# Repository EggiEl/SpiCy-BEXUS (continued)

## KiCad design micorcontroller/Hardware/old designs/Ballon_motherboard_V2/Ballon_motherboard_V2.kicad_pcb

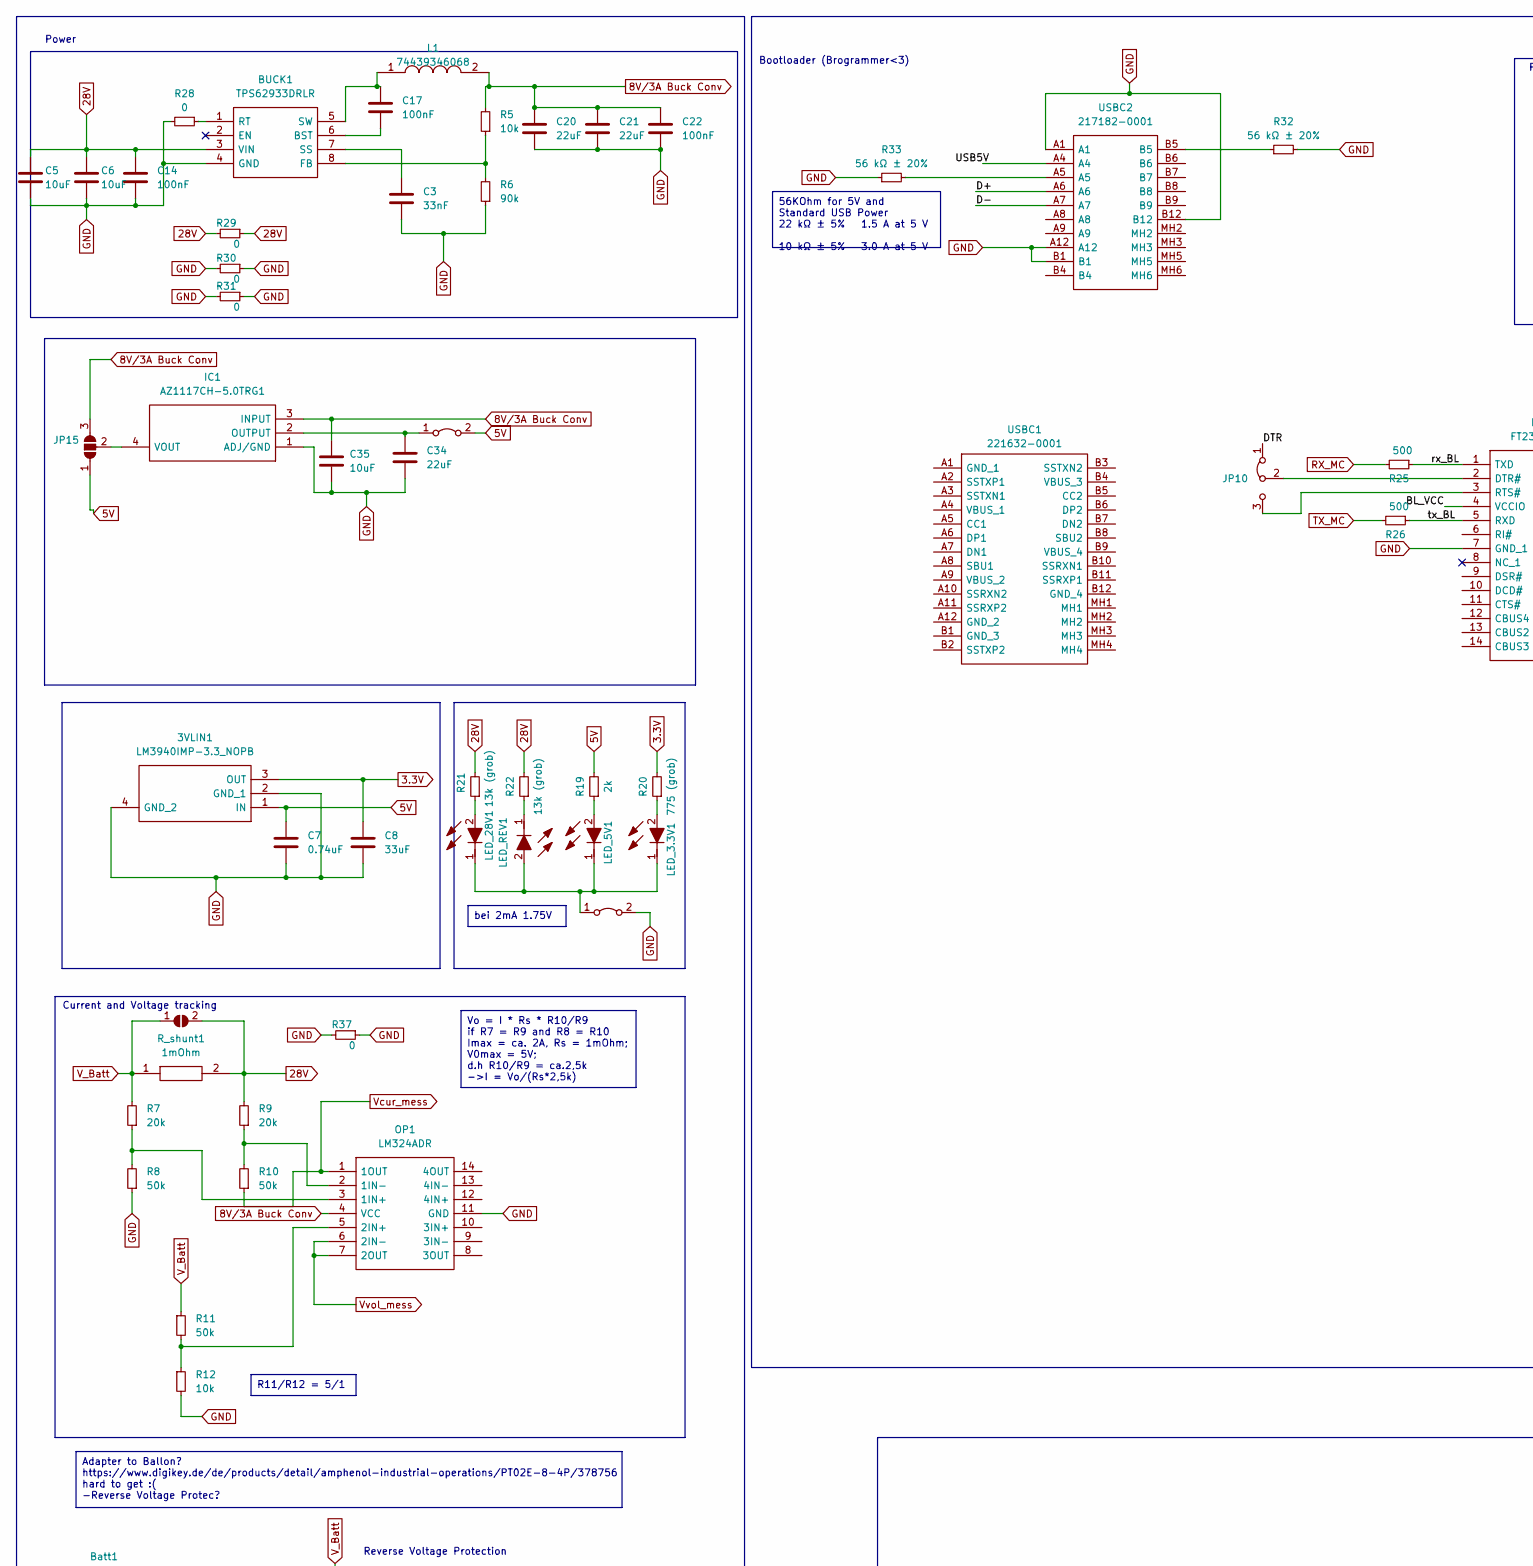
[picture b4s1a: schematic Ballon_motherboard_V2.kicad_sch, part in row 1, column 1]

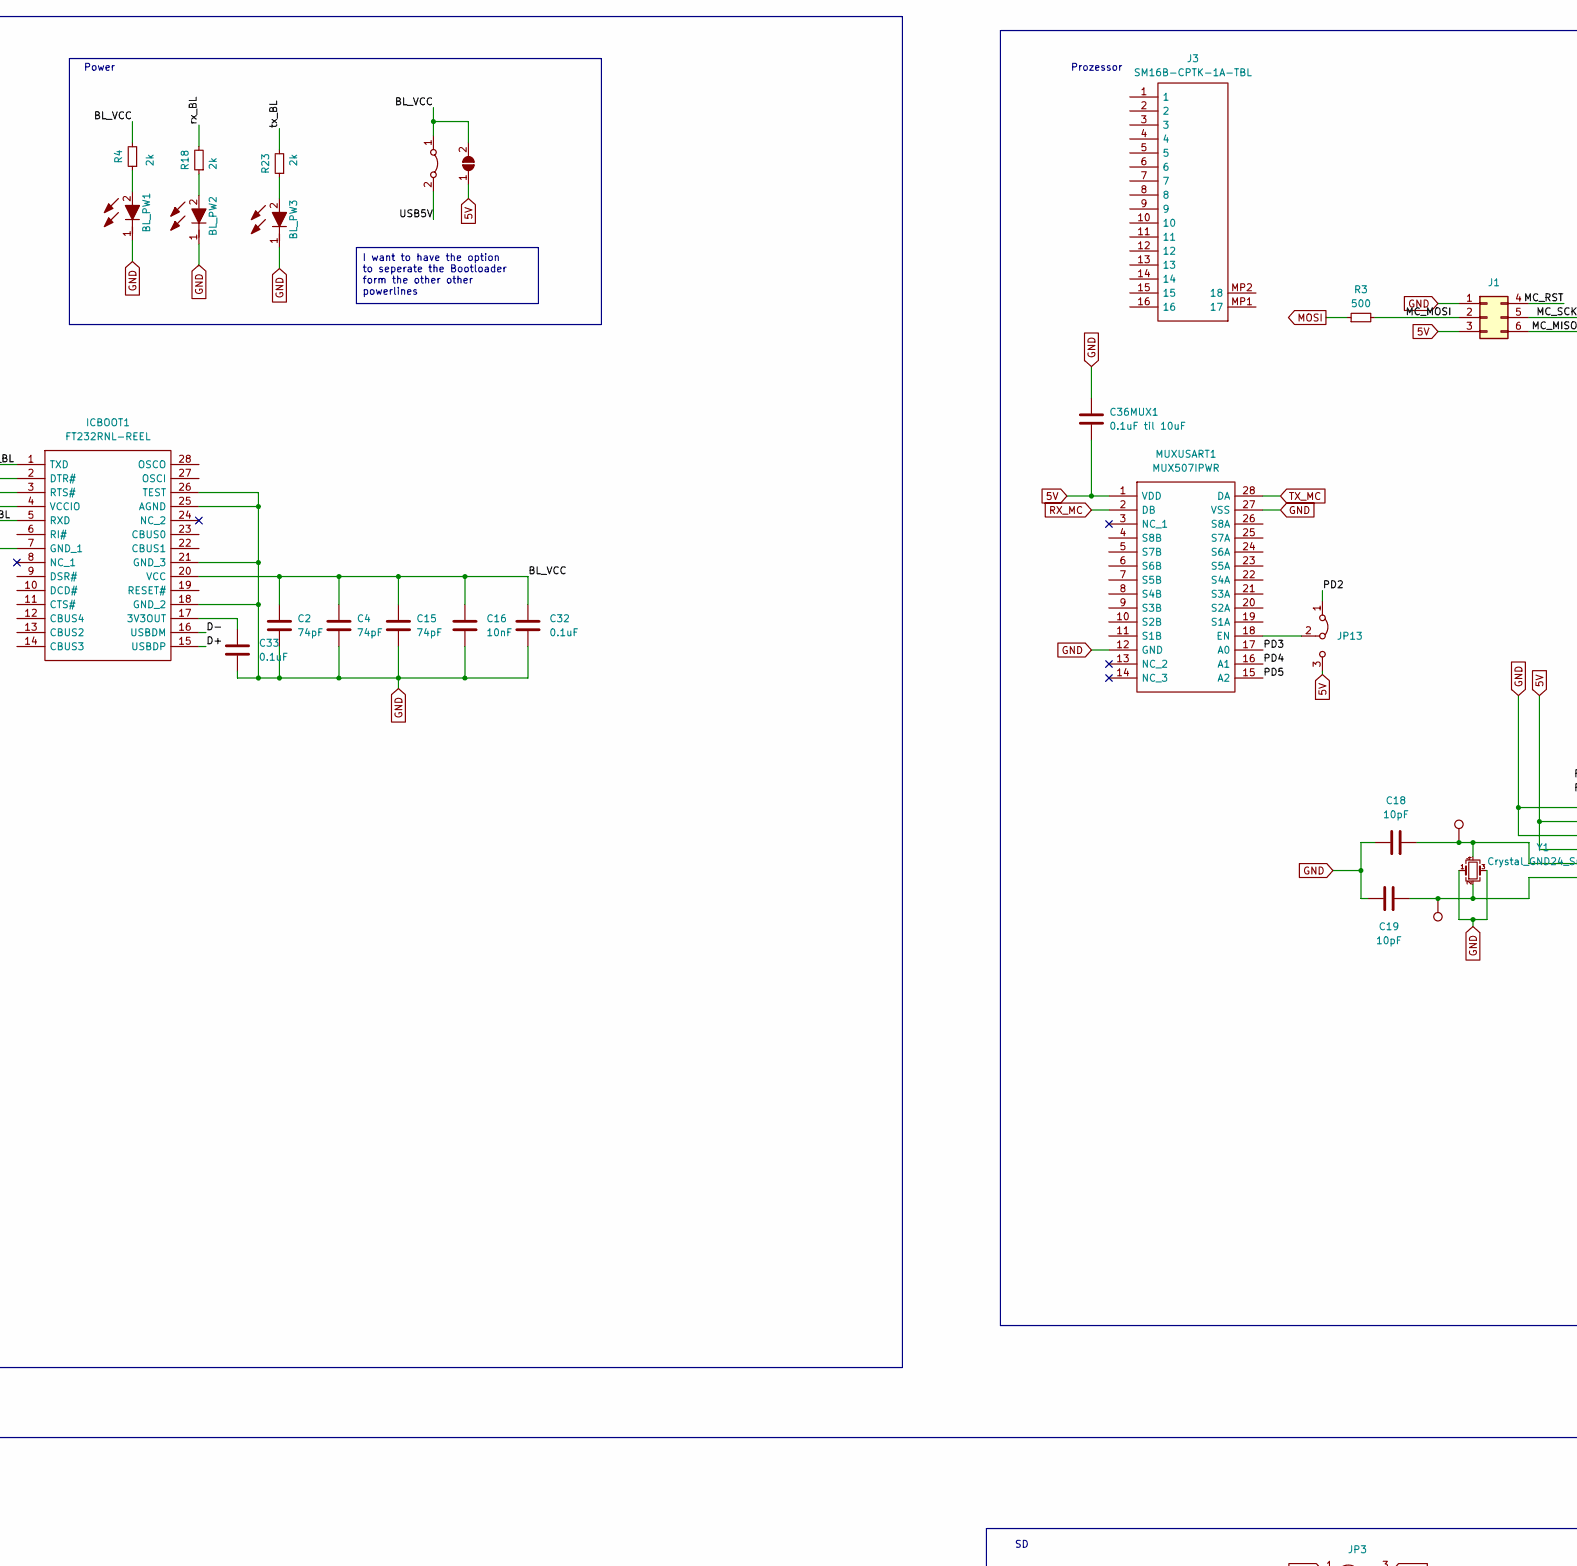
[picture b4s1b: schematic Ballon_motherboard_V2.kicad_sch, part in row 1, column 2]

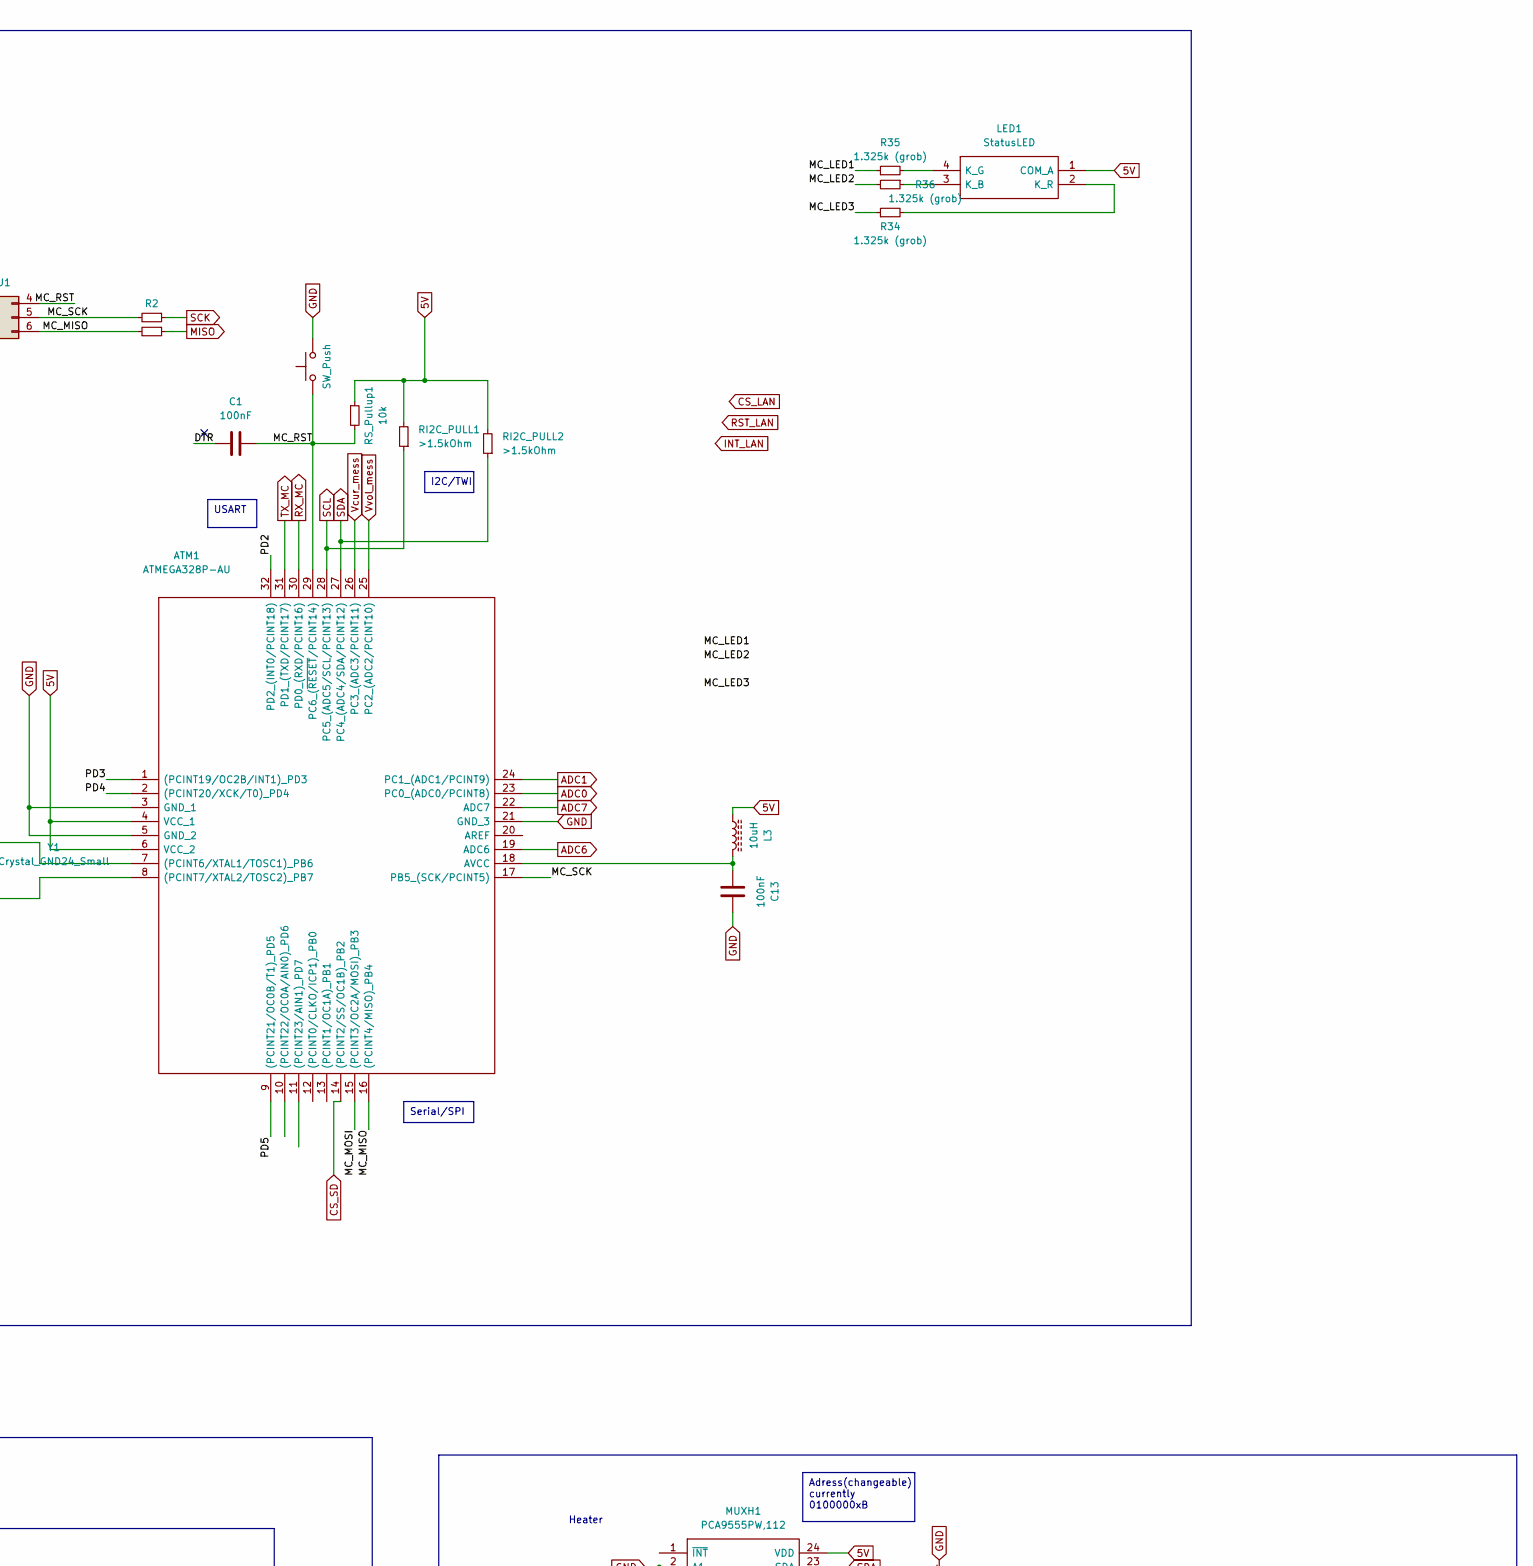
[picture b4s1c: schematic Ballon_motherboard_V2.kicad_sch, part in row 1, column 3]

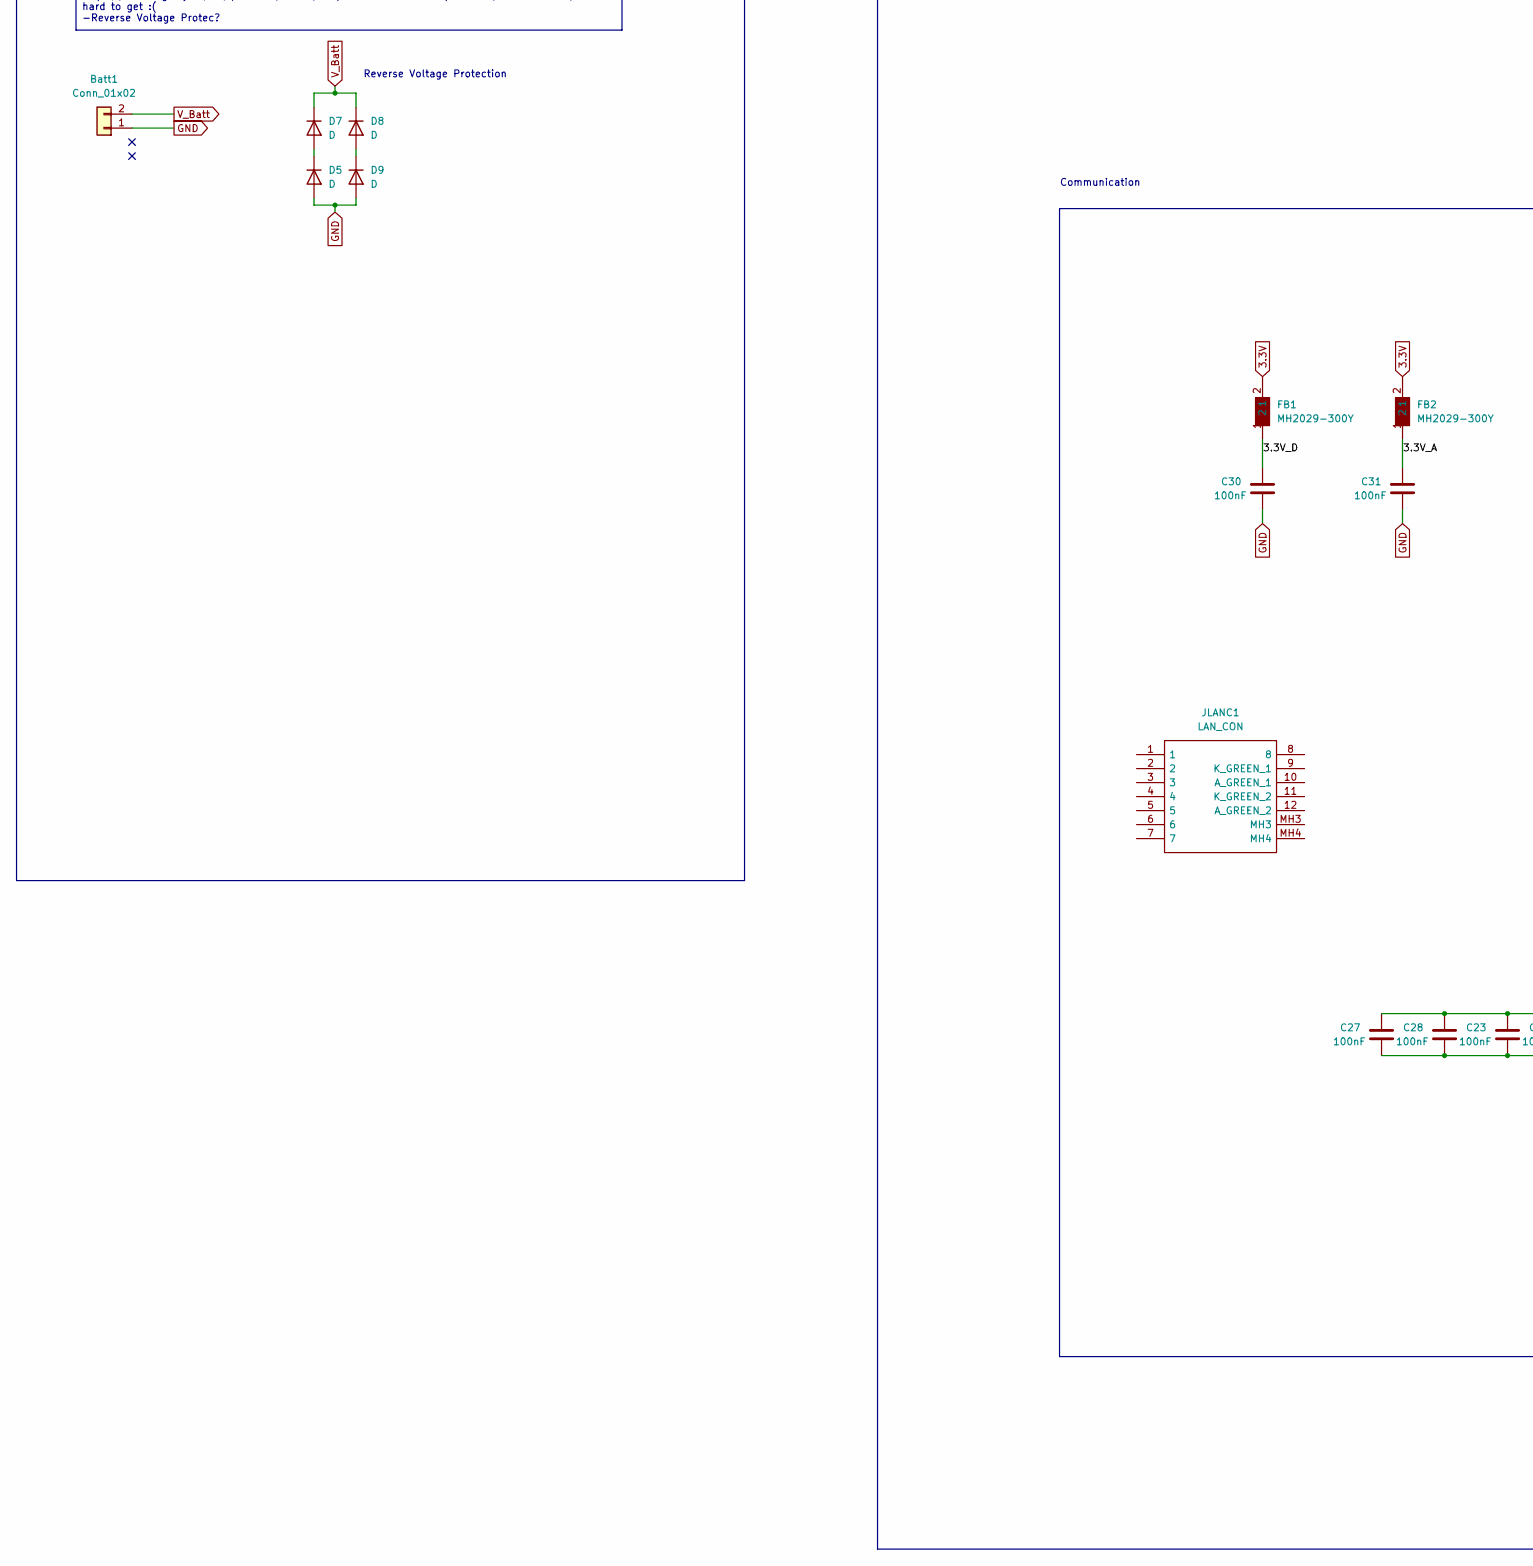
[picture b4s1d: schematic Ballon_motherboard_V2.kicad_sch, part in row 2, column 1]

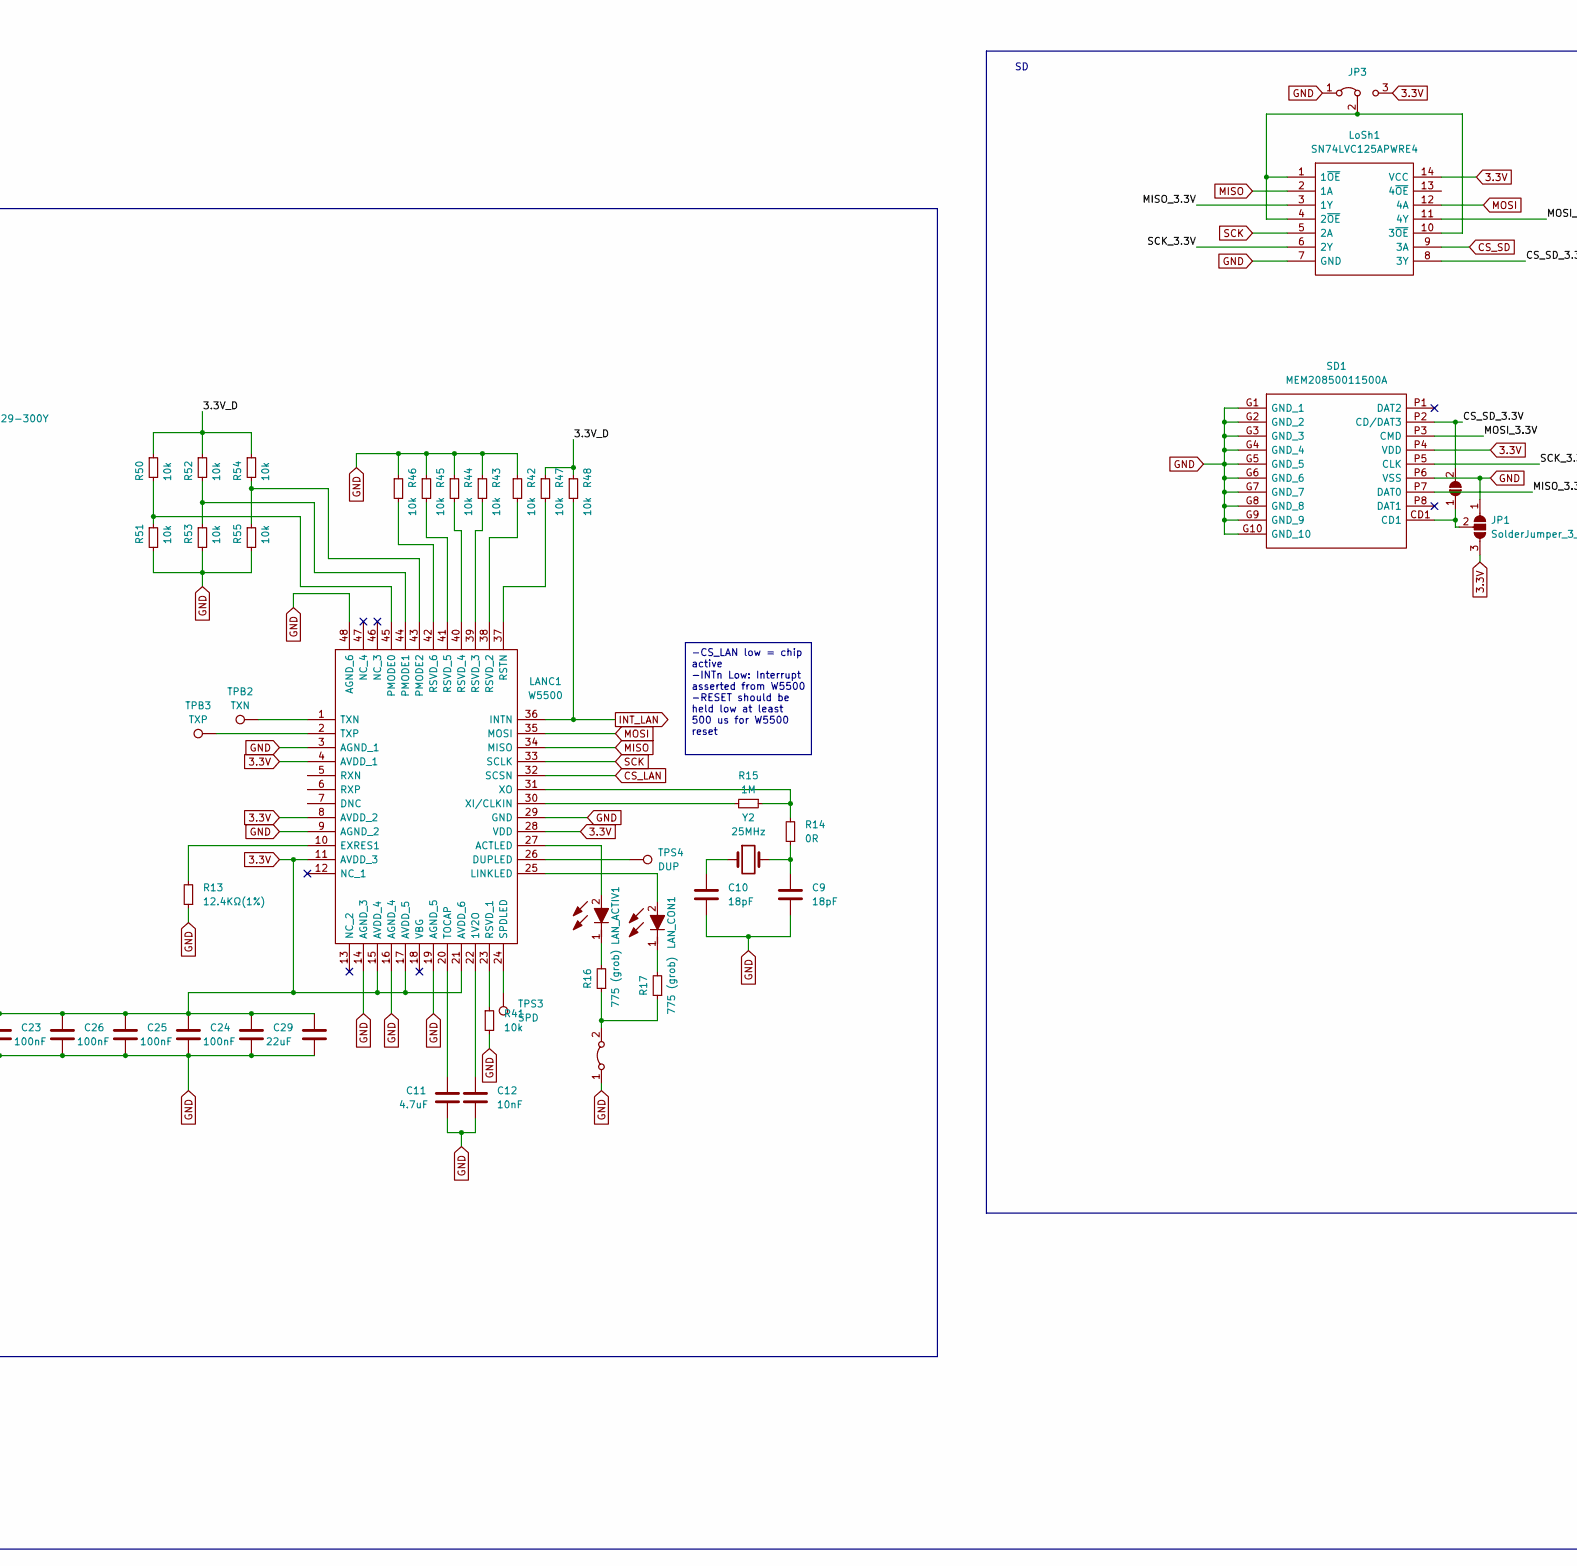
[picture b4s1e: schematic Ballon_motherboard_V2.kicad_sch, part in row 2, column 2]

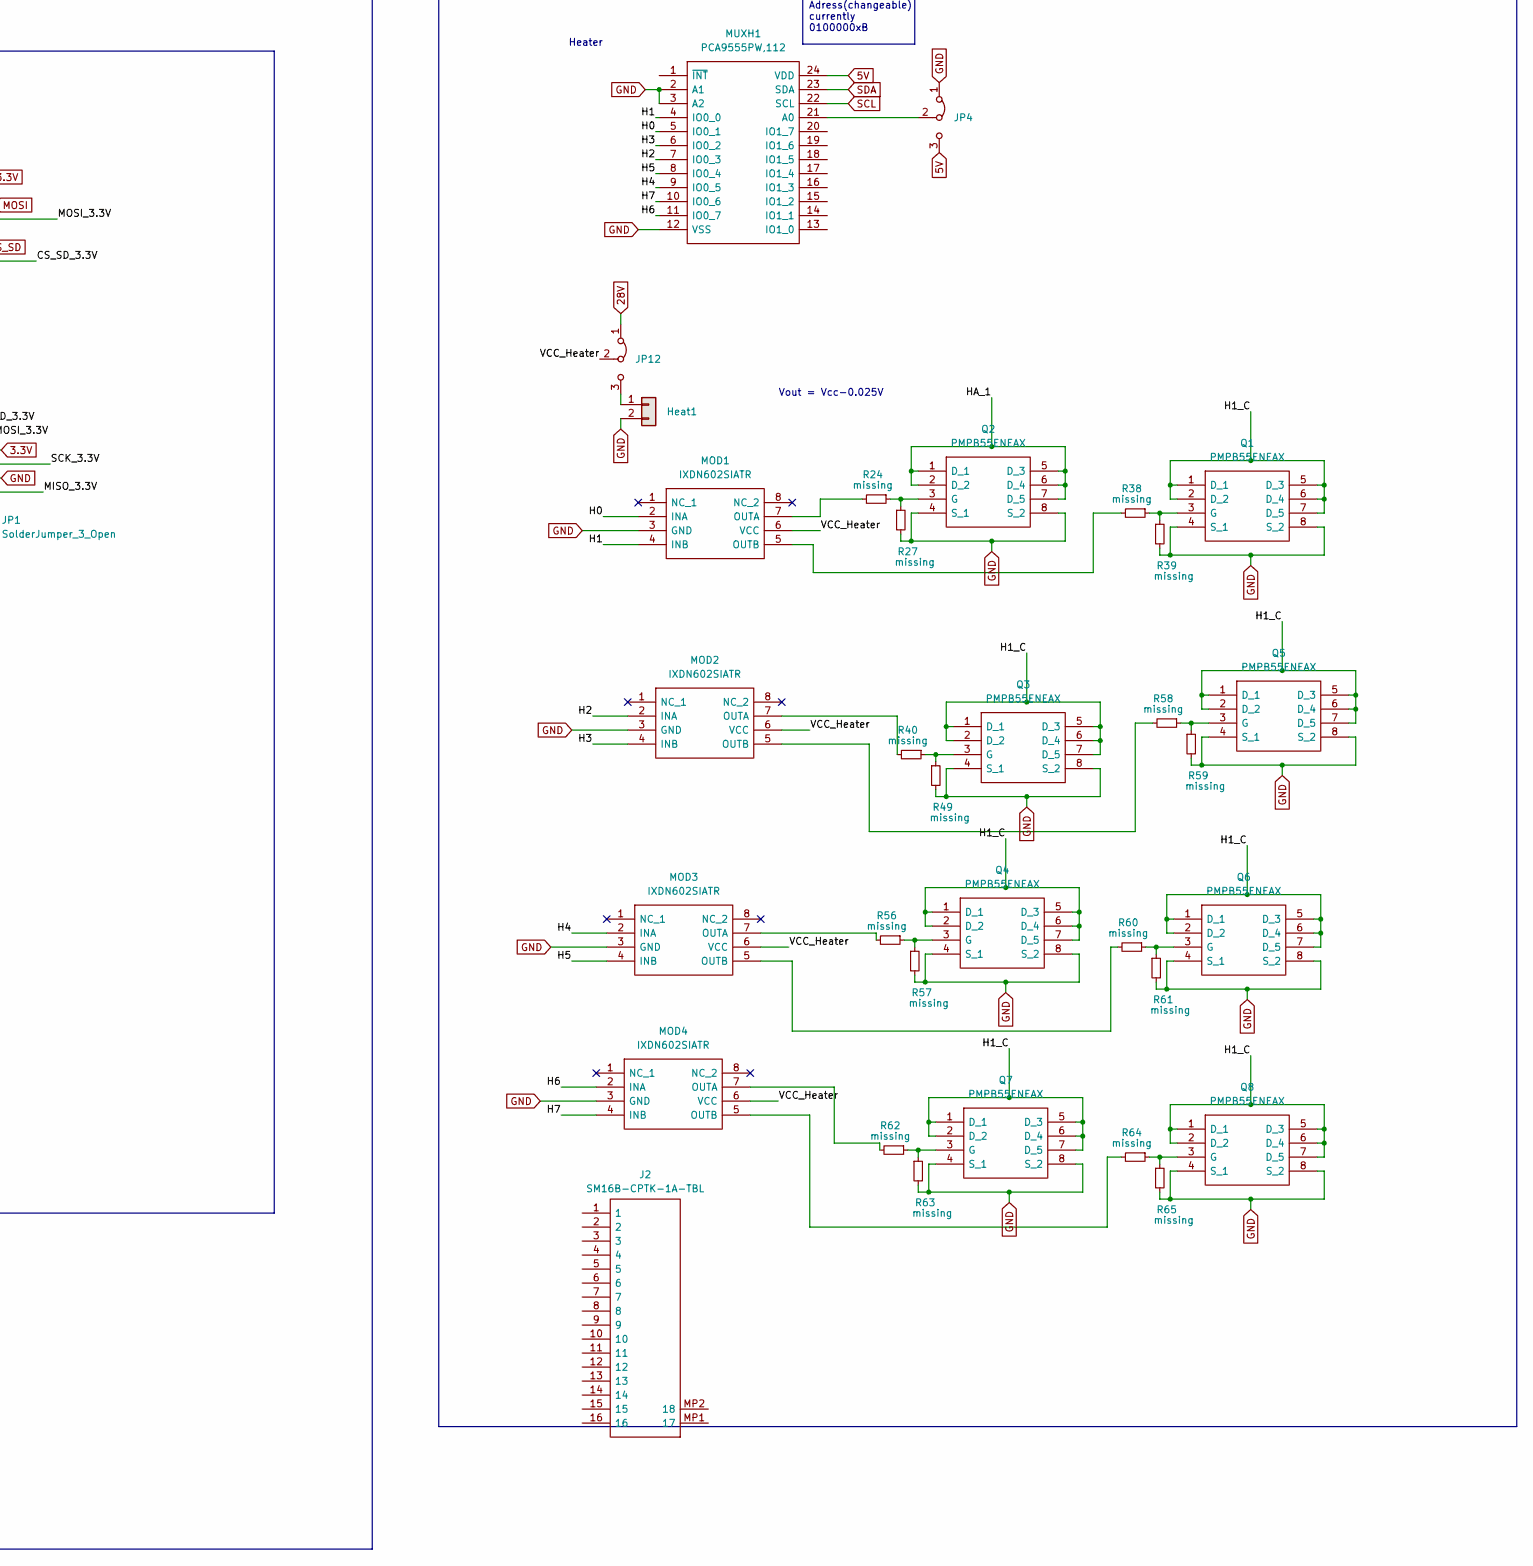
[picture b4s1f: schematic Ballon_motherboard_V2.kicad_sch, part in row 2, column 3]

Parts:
3VLIN1: LM3940IMP-3.3_NOPB; SOT230P700X180-4N; Mouser Part Number 926-LM3940IMP3.3NOPB
ATM1: ATMEGA328P-AU; QFP80P900X900X120-32N; Mouser Part Number 556-ATMEGA328P-AU
BL_PW1, BL_PW2, BL_PW3: APTD2012LSURCK; LEDM2012X120N; Mouser Part Number 604-APTD2012LSURCK
BUCK1: TPS62933DRLR; SOTFL50P160X60-8N; Mouser Part Number 595-TPS62933DRLR
Batt1: Conn_01x02; PinHeader_1x02_P2.54mm_Vertical
C1, C13, C14, C17, C22, C23, C24, C25, C26, C27, C28, C30, C31: 100nF; C_0603_1608Metric
C2, C4, C15: 74pF; C_0603_1608Metric
C3: 33nF; C_0603_1608Metric
C5, C6, C35: 10uF; C_0603_1608Metric
C7: 0.74uF; C_0603_1608Metric
C8: 33uF; C_0603_1608Metric
C9, C10: 18pF; C_0603_1608Metric
C11: 4.7uF; C_0603_1608Metric
C12, C16: 10nF; C_0603_1608Metric
C18, C19: 10pF; C_0603_1608Metric
C20, C21, C29, C34: 22uF; C_0603_1608Metric
C32, C33: 0.1uF; C_0603_1608Metric
C36MUX1: 0.1uF til 10uF; C_0603_1608Metric
D5, D7, D8, D9: D
FB1, FB2: MH2029-300Y; BEADC2016X130N; Mouser Part Number 652-MH2029-300Y
Heat1: Conn_01x02; PinHeader_1x02_P2.54mm_Vertical
IC1: AZ1117CH-5.0TRG1; SOT230P700X180-4N; Mouser Part Number 621-AZ1117CH-5.0TRG1
ICBOOT1: FT232RNL-REEL; SOP65P780X200-28N; Mouser Part Number 895-FT232RNL-REEL
J1: Conn_02x03_Top_Bottom; PinHeader_2x03_P2.54mm_Vertical
J2, J3: SM16B-CPTK-1A-TBL; SM16BCPTK1ATBL; Mouser Part Number 306-SM16B-CPTK-1ATBL
JLANC1: LAN_CON; MJ323088GG2; Mouser Part Number 640-MJ323088GG2
JP1, JP15: SolderJumper_3_Open; SolderJumper-3_P1.3mm_Open_RoundedPad1.0x1.5mm_NumberLabels
JP2, JP8, JP11: SolderJumper_2_Open; SolderJumper-2_P1.3mm_Open_Pad1.0x1.5mm
JP3, JP4, JP10, JP12, JP13: Jumper_3_Bridged12; SolderJumper-3_P1.3mm_Bridged12_RoundedPad1.0x1.5mm_NumberL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
JP5, JP6, JP7, JP9: Jumper_2_Bridged; SolderJumper-2_P1.3mm_Bridged2Bar_RoundedPad1.0x1.5mm
L1: 74439346068; Mouser Part Number 710-74439346068
L3: 10uH
LANC1: W5500; QFP50P900X900X160-48N; Mouser Part Number 950-W5500
LAN_ACTIV1: APTD2012LSURCK; LEDM2012X120N; Mouser Part Number 604-APTD2012LSURCK
LAN_CON1: APTD2012LSURCK; LEDM2012X120N; Mouser Part Number 604-APTD2012LSURCK
LED1: StatusLED; LTRBR37G4R4S01250; Mouser Part Number 720-LTRBR37GA6714
LED_3.3V1, LED_5V1, LED_28V1: APTD2012LSURCK; LEDM2012X120N; Mouser Part Number 604-APTD2012LSURCK
LED_REV1: APTD2012LSURCK; LEDM2012X120N; Mouser Part Number 604-APTD2012LSURCK
LoSh1: SN74LVC125APWRE4; Mouser Part Number 595-SN74LVC125APWRE4
MOD1, MOD2, MOD3, MOD4: IXDN602SIATR; SOIC127P600X175-8N; Mouser Part Number 849-IXDN602SIATR
MUXH1: PCA9555PW,112; SOP65P640X110-24N; Mouser Part Number 771-PCA9555PW
MUXUSART1: MUX507IPWR; SOP65P640X120-28N; Mouser Part Number 595-MUX507IPWR
OP1: LM324ADR; SOIC127P600X175-14N; Mouser Part Number 595-LM324ADR
Q1, Q2, Q3, Q4, Q5, Q6, Q7, Q8: PMPB55ENEAX; Mouser Part Number 771-PMPB55ENEAX
R1, R2, R3: 500; R_0805_2012Metric_Pad1.20x1.40mm_HandSolder
R4, R18, R19, R23: 2k; R_0805_2012Metric_Pad1.20x1.40mm_HandSolder
R5, R12, R41, R42, R43, R44, R45, R46, R47, R48, R50, R51, R52, R53, R54, R55: 10k; R_0805_2012Metric_Pad1.20x1.40mm_HandSolder
R6: 90k; R_0805_2012Metric_Pad1.20x1.40mm_HandSolder
R7, R9: 20k; R_0805_2012Metric_Pad1.20x1.40mm_HandSolder
R8, R10, R11: 50k; R_0805_2012Metric_Pad1.20x1.40mm_HandSolder
R13: 12.4KΩ(1%); R_0805_2012Metric_Pad1.20x1.40mm_HandSolder
R14: 0R; R_0805_2012Metric
R15: 1M; R_0805_2012Metric_Pad1.20x1.40mm_HandSolder
R16, R17, R20: 775 (grob); R_0805_2012Metric_Pad1.20x1.40mm_HandSolder
R21, R22: 13k (grob); R_0805_2012Metric_Pad1.20x1.40mm_HandSolder
R24, R27, R38, R39, R40, R49, R56, R57, R58, R59, R60, R61, R62, R63, R64, R65: missing; R_0805_2012Metric_Pad1.20x1.40mm_HandSolder
R25, R26: 500; R_Axial_DIN0204_L3.6mm_D1.6mm_P5.08mm_Vertical
R28: 0; R_0805_2012Metric_Pad1.20x1.40mm_HandSolder
R29, R30, R31, R37: 0; R_1206_3216Metric
R32, R33: 56 kΩ ± 20%; R_0805_2012Metric_Pad1.20x1.40mm_HandSolder
R34, R35, R36: 1.325k (grob); R_0805_2012Metric_Pad1.20x1.40mm_HandSolder
RI2C_PULL1, RI2C_PULL2: >1.5kOhm; R_0805_2012Metric_Pad1.20x1.40mm_HandSolder
RS_Pullup1: 10k; R_0805_2012Metric_Pad1.20x1.40mm_HandSolder
R_shunt1: 1mOhm; RESC3216X90N; Mouser Part Number 603-PA1206FRE7W0R01Z
SD1: MEM20850011500A; Mouser Part Number 640-MEM20850011500A
SW1: SW_Push
TPB2: TXN; TestPoint_Pad_D2.0mm
TPB3: TXP; TestPoint_Pad_D2.0mm
TPS3: SPD; TestPoint_Pad_D1.0mm
TPS4: DUP; TestPoint_Pad_D1.0mm
TPS17, TPS18: TestPoint; TestPoint_Pad_D1.0mm
USBC1: 221632-0001; Mouser Part Number 538-221632-0001
USBC2: 217182-0001; 2171820001; Mouser Part Number 538-217182-0001
Y1: Crystal_GND24_Small; ECS1601037B2JTNTR
Y2: 25MHz

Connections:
3.3V: 3VLIN1.3 (OUT), C8.2, C23.1, C24.1, C25.1, C26.1, C27.1, C28.1, C29.1, FB1.2, FB2.2, JP1.3 (B), JP3.3 (B), LANC1.4 (AVDD_1), LANC1.8 (AVDD_2), LANC1.11 (AVDD_3), LANC1.15 (AVDD_4), LANC1.17 (AVDD_5), LANC1.21 (AVDD_6), LANC1.28 (VDD), LoSh1.14 (VCC), R20.2, SD1.P4 (VDD)
5V: 3VLIN1.1 (IN), ATM1.4 (VCC_1), ATM1.6 (VCC_2), C7.2, C36MUX1.2, J1.3, JP4.3 (B), JP5.2 (B), JP8.1 (A), JP13.3 (B), JP15.1 (A), L3.1, LED1.1 (COM_A), MUXH1.24 (VDD), MUXUSART1.1 (VDD), R19.2, RI2C_PULL1.2, RI2C_PULL2.2, RS_Pullup1.1
8V/3A Buck Conv: C20.2, C21.2, C22.2, C35.2, IC1.3 (INPUT), JP15.3 (B), L1.2, OP1.4 (VCC), R5.2
28V: BUCK1.3 (VIN), C5.2, C6.2, C14.2, JP2.2 (B), JP12.1 (A), R9.2, R21.2, R22.2, R29.1, R29.2, R_shunt1.2
/3.3V_A: C31.1, FB2.1
/3.3V_D: C30.1, FB1.1, R47.1, R48.1, R50.1, R52.1, R54.1
/BL_VCC: C2.2, C4.2, C15.2, C16.2, C32.2, ICBOOT1.4 (VCCIO), ICBOOT1.20 (VCC), JP8.2 (B), JP9.1 (A), R4.2
/CS_SD_3.3V: JP11.2 (B), LoSh1.8 (3Y), SD1.P2 (CD/DAT3)
/D+: ICBOOT1.15 (USBDP), USBC2.A6
/D-: ICBOOT1.16 (USBDM), USBC2.A7
/DTR: C1.1, JP10.1 (A)
/H0: MOD1.2 (INA), MUXH1.5 (IO0_1)
/H1: MOD1.4 (INB), MUXH1.4 (IO0_0)
/H1_C: Q1.1 (D_1), Q1.2 (D_2), Q1.5 (D_3), Q1.6 (D_4), Q1.7 (D_5), Q3.1 (D_1), Q3.2 (D_2), Q3.5 (D_3), Q3.6 (D_4), Q3.7 (D_5), Q4.1 (D_1), Q4.2 (D_2), Q4.5 (D_3), Q4.6 (D_4), Q4.7 (D_5), Q5.1 (D_1), Q5.2 (D_2), Q5.5 (D_3), Q5.6 (D_4), Q5.7 (D_5), Q6.1 (D_1), Q6.2 (D_2), Q6.5 (D_3), Q6.6 (D_4), Q6.7 (D_5), Q7.1 (D_1), Q7.2 (D_2), Q7.5 (D_3), Q7.6 (D_4), Q7.7 (D_5), Q8.1 (D_1), Q8.2 (D_2), Q8.5 (D_3), Q8.6 (D_4), Q8.7 (D_5)
/H2: MOD2.2 (INA), MUXH1.7 (IO0_3)
/H3: MOD2.4 (INB), MUXH1.6 (IO0_2)
/H4: MOD3.2 (INA), MUXH1.9 (IO0_5)
/H5: MOD3.4 (INB), MUXH1.8 (IO0_4)
/H6: MOD4.2 (INA), MUXH1.11 (IO0_7)
/H7: MOD4.4 (INB), MUXH1.10 (IO0_6)
/HA_1: Q2.1 (D_1), Q2.2 (D_2), Q2.5 (D_3), Q2.6 (D_4), Q2.7 (D_5)
/MC_LED1: R35.1
/MC_LED2: R36.2
/MC_LED3: R34.1
/MC_MISO: ATM1.16 ((PCINT4/MISO)_PB4), J1.6, R1.2
/MC_MOSI: ATM1.15 ((PCINT3/OC2A/MOSI)_PB3), J1.2, R3.2
/MC_RST: ATM1.29 (PC6_(~RESET/PCINT14)), C1.2, J1.4, RS_Pullup1.2, SW1.1
/MC_SCK: ATM1.17 (PB5_(SCK/PCINT5)), J1.5, R2.2
/MISO_3.3V: LoSh1.3 (1Y), SD1.P7 (DAT0)
/MOSI_3.3V: LoSh1.11 (4Y), SD1.P3 (CMD)
/PD2: ATM1.32 (PD2_(INT0/PCINT18)), JP13.1 (A)
/PD3: ATM1.1 ((PCINT19/OC2B/INT1)_PD3), MUXUSART1.17 (A0)
/PD4: ATM1.2 ((PCINT20/XCK/T0)_PD4), MUXUSART1.16 (A1)
/PD5: ATM1.9 ((PCINT21/OC0B/T1)_PD5), MUXUSART1.15 (A2)
/SCK_3.3V: LoSh1.6 (2Y), SD1.P5 (CLK)
/USB5V: JP9.2 (B), USBC2.A4
/VCC_Heater: JP12.2 (C), MOD1.6 (VCC), MOD2.6 (VCC), MOD3.6 (VCC), MOD4.6 (VCC)
/rx_BL: ICBOOT1.1 (TXD), R18.2, R25.1
/tx_BL: ICBOOT1.5 (RXD), R23.2, R26.1
ADC0: ATM1.23 (PC0_(ADC0/PCINT8))
ADC1: ATM1.24 (PC1_(ADC1/PCINT9))
ADC6: ATM1.19 (ADC6)
ADC7: ATM1.22 (ADC7)
CS_LAN: LANC1.32 (SCSN)
CS_SD: ATM1.14 ((PCINT2/SS/OC1B)_PB2), LoSh1.9 (3A)
GND: 3VLIN1.2 (GND_1), 3VLIN1.4 (GND_2), ATM1.3 (GND_1), ATM1.5 (GND_2), ATM1.21 (GND_3), BL_PW1.1, BL_PW2.1, BL_PW3.1, BUCK1.4 (GND), Batt1.1, C2.1, C3.1, C4.1, C5.1, C6.1, C7.1, C8.1, C9.2, C10.2, C11.2, C12.2, C13.2, C14.1, C15.1, C16.1, C18.1, C19.1, C20.1, C21.1, C22.1, C23.2, C24.2, C25.2, C26.2, C27.2, C28.2, C29.2, C30.2, C31.2, C32.1, C33.1, C34.1, C35.1, C36MUX1.1, D5.2 (A), D9.2 (A), Heat1.2, IC1.1 (ADJ/GND), ICBOOT1.7 (GND_1), ICBOOT1.18 (GND_2), ICBOOT1.21 (GND_3), ICBOOT1.25 (AGND), ICBOOT1.26 (TEST), J1.1, JP1.1 (A), JP3.1 (A), JP4.1 (A), JP6.2 (B), JP7.1 (A), LANC1.3 (AGND_1), LANC1.9 (AGND_2), LANC1.14 (AGND_3), LANC1.16 (AGND_4), LANC1.19 (AGND_5), LANC1.29 (GND), LANC1.48 (AGND_6), LoSh1.7 (GND), MOD1.3 (GND), MOD2.3 (GND), MOD3.3 (GND), MOD4.3 (GND), MUXH1.2 (A1), MUXH1.3 (A2), MUXH1.12 (VSS), MUXUSART1.12 (GND), MUXUSART1.27 (VSS), OP1.11 (GND), Q1.4 (S_1), Q1.8 (S_2), Q2.4 (S_1), Q2.8 (S_2), Q3.4 (S_1), Q3.8 (S_2), Q4.4 (S_1), Q4.8 (S_2), Q5.4 (S_1), Q5.8 (S_2), Q6.4 (S_1), Q6.8 (S_2), Q7.4 (S_1), Q7.8 (S_2), Q8.4 (S_1), Q8.8 (S_2), R6.1, R8.1, R12.2, R13.1, R27.2, R28.2, R30.1, R30.2, R31.1, R31.2, R32.2, R33.1, R37.1, R37.2, R39.2, R41.2, R42.1, R43.1, R44.1, R45.1, R46.1, R49.2, R51.2, R53.2, R55.2, R57.2, R59.2, R61.2, R63.2, R65.2, SD1.G1 (GND_1), SD1.G2 (GND_2), SD1.G3 (GND_3), SD1.G4 (GND_4), SD1.G5 (GND_5), SD1.G6 (GND_6), SD1.G7 (GND_7), SD1.G8 (GND_8), SD1.G9 (GND_9), SD1.G10 (GND_10), SD1.P6 (VSS), SW1.2, USBC2.A1, USBC2.A12, USBC2.B1, USBC2.B12, Y1.1, Y1.3
INT_LAN: LANC1.36 (INTN), R48.2
MISO: LANC1.34 (MISO), LoSh1.2 (1A), R1.1
MOSI: LANC1.35 (MOSI), LoSh1.12 (4A), R3.1
unnamed: ATM1.7 ((PCINT6/XTAL1/TOSC1)_PB6), C18.2, TPS17.1, Y1.4
unnamed: ATM1.8 ((PCINT7/XTAL2/TOSC2)_PB7), C19.2, TPS18.1, Y1.2
unnamed: ATM1.18 (AVCC), C13.1, L3.2
unnamed: BL_PW1.2, R4.1
unnamed: BL_PW2.2, R18.1
unnamed: BL_PW3.2, R23.1
unnamed: BUCK1.6 (BST), C17.1
unnamed: BUCK1.8 (FB), R5.1, R6.2
unnamed: BUCK1.1 (RT), R28.1
unnamed: BUCK1.7 (SS), C3.2
unnamed: BUCK1.5 (SW), C17.2, L1.1
unnamed: C9.1, R14.1, Y2.2
unnamed: C10.1, Y2.1
unnamed: D5.1 (K), D7.2 (A)
unnamed: D8.2 (A), D9.1 (K)
unnamed: Heat1.1, JP12.3 (B)
unnamed: C34.2, IC1.2 (OUTPUT), JP5.1 (A)
unnamed: IC1.4 (VOUT), JP15.2 (C)
unnamed: C33.2, ICBOOT1.17 (3V3OUT)
unnamed: ICBOOT1.2 (DTR#), JP10.2 (C)
unnamed: ICBOOT1.3 (RTS#), JP10.3 (B)
unnamed: JP1.2 (C), JP11.1 (A), SD1.CD1
unnamed: JP3.2 (C), LoSh1.1 (1~OE), LoSh1.4 (2~OE), LoSh1.10 (3~OE)
unnamed: JP4.2 (C), MUXH1.21 (A0)
unnamed: JP6.1 (A), LED_3.3V1.1, LED_5V1.1, LED_28V1.1, LED_REV1.2
unnamed: JP7.2 (B), R16.1, R17.1
unnamed: JP13.2 (C), MUXUSART1.18 (EN)
unnamed: C12.1, LANC1.22 (1V2O)
unnamed: LANC1.27 (ACTLED), LAN_ACTIV1.2
unnamed: LANC1.26 (DUPLED), TPS4.1
unnamed: LANC1.10 (EXRES1), R13.2
unnamed: LANC1.25 (LINKLED), LAN_CON1.2
unnamed: LANC1.45 (PMODE0), R50.2, R51.1
unnamed: LANC1.44 (PMODE1), R52.2, R53.1
unnamed: LANC1.43 (PMODE2), R54.2, R55.1
unnamed: LANC1.37 (RSTN), R47.2
unnamed: LANC1.23 (RSVD_1), R41.1
unnamed: LANC1.38 (RSVD_2), R42.2
unnamed: LANC1.39 (RSVD_3), R43.2
unnamed: LANC1.40 (RSVD_4), R44.2
unnamed: LANC1.41 (RSVD_5), R45.2
unnamed: LANC1.42 (RSVD_6), R46.2
unnamed: LANC1.24 (SPDLED), TPS3.1
unnamed: C11.1, LANC1.20 (TOCAP)
unnamed: LANC1.1 (TXN), TPB2.1
unnamed: LANC1.2 (TXP), TPB3.1
unnamed: LANC1.30 (XI/CLKIN), R15.2
unnamed: LANC1.31 (XO), R14.2, R15.1
unnamed: LAN_ACTIV1.1, R16.2
unnamed: LAN_CON1.1, R17.2
unnamed: LED1.3 (K_B), R36.1
unnamed: LED1.4 (K_G), R35.2
unnamed: LED1.2 (K_R), R34.2
unnamed: LED_3.3V1.2, R20.1
unnamed: LED_5V1.2, R19.1
unnamed: LED_28V1.2, R21.1
unnamed: LED_REV1.1, R22.1
unnamed: MOD1.7 (OUTA), R24.2
unnamed: MOD1.5 (OUTB), R38.2
unnamed: MOD2.7 (OUTA), R40.2
unnamed: MOD2.5 (OUTB), R58.2
unnamed: MOD3.7 (OUTA), R56.2
unnamed: MOD3.5 (OUTB), R60.2
unnamed: MOD4.7 (OUTA), R62.2
unnamed: MOD4.5 (OUTB), R64.2
unnamed: OP1.3 (1IN+), R7.1, R8.2
unnamed: OP1.2 (1IN-), R9.1, R10.2
unnamed: OP1.5 (2IN+), R11.2, R12.1
unnamed: Q1.3 (G), R38.1, R39.1
unnamed: Q2.3 (G), R24.1, R27.1
unnamed: Q3.3 (G), R40.1, R49.1
unnamed: Q4.3 (G), R56.1, R57.1
unnamed: Q5.3 (G), R58.1, R59.1
unnamed: Q6.3 (G), R60.1, R61.1
unnamed: Q7.3 (G), R62.1, R63.1
unnamed: Q8.3 (G), R64.1, R65.1
unnamed: R32.1, USBC2.B5
unnamed: R33.2, USBC2.A5
RX_MC: ATM1.30 (PD0_(RXD/PCINT16)), MUXUSART1.2 (DB), R25.2
SCK: LANC1.33 (SCLK), LoSh1.5 (2A), R2.1
SCL: ATM1.28 (PC5_(ADC5/SCL/PCINT13)), MUXH1.22 (SCL), RI2C_PULL1.1
SDA: ATM1.27 (PC4_(ADC4/SDA/PCINT12)), MUXH1.23 (SDA), RI2C_PULL2.1
TX_MC: ATM1.31 (PD1_(TXD/PCINT17)), MUXUSART1.28 (DA), R26.2
V_Batt: Batt1.2, D7.1 (K), D8.1 (K), JP2.1 (A), R7.2, R11.1, R_shunt1.1
Vcur_mess: ATM1.26 (PC3_(ADC3/PCINT11)), OP1.1 (1OUT), R10.1
Vvol_mess: ATM1.25 (PC2_(ADC2/PCINT10)), OP1.6 (2IN-), OP1.7 (2OUT)

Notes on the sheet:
bei 2mA 1.75V
I want to have the option to seperate the Bootloader form the other other powerlines
Adapter to Ballon? https://www.digikey.de/de/products/detail/amphenol-industrial-operations/PT02E-8-4P/378756 hard to get :( -Reverse Voltage Protec?
Serial/SPI
USART
R11/R12 = 5/1
Adress(changeable) currently 0100000xB
I2C/TWI
Vo = I * Rs * R10/R9 if R7 = R9 and R8 = R10 Imax = ca. 2A, Rs = 1mOhm; V0max = 5V; d.h R10/R9 = ca.2,5k ->I = Vo/(Rs*2,5k)
-CS_LAN low = chip active -INTn Low: Interrupt asserted from W5500 -RESET should be held low at least 500 us for W5500 reset
56KOhm for 5V and Standard USB Power 22 kΩ ± 5% 1.5 A at 5 V 10 kΩ ± 5% 3.0 A at 5 V
Vout = Vcc-0.025V
Bootloader (Brogrammer<3)
Heater
Reverse Voltage Protection
Current and Voltage tracking
Power
Prozessor
Communication

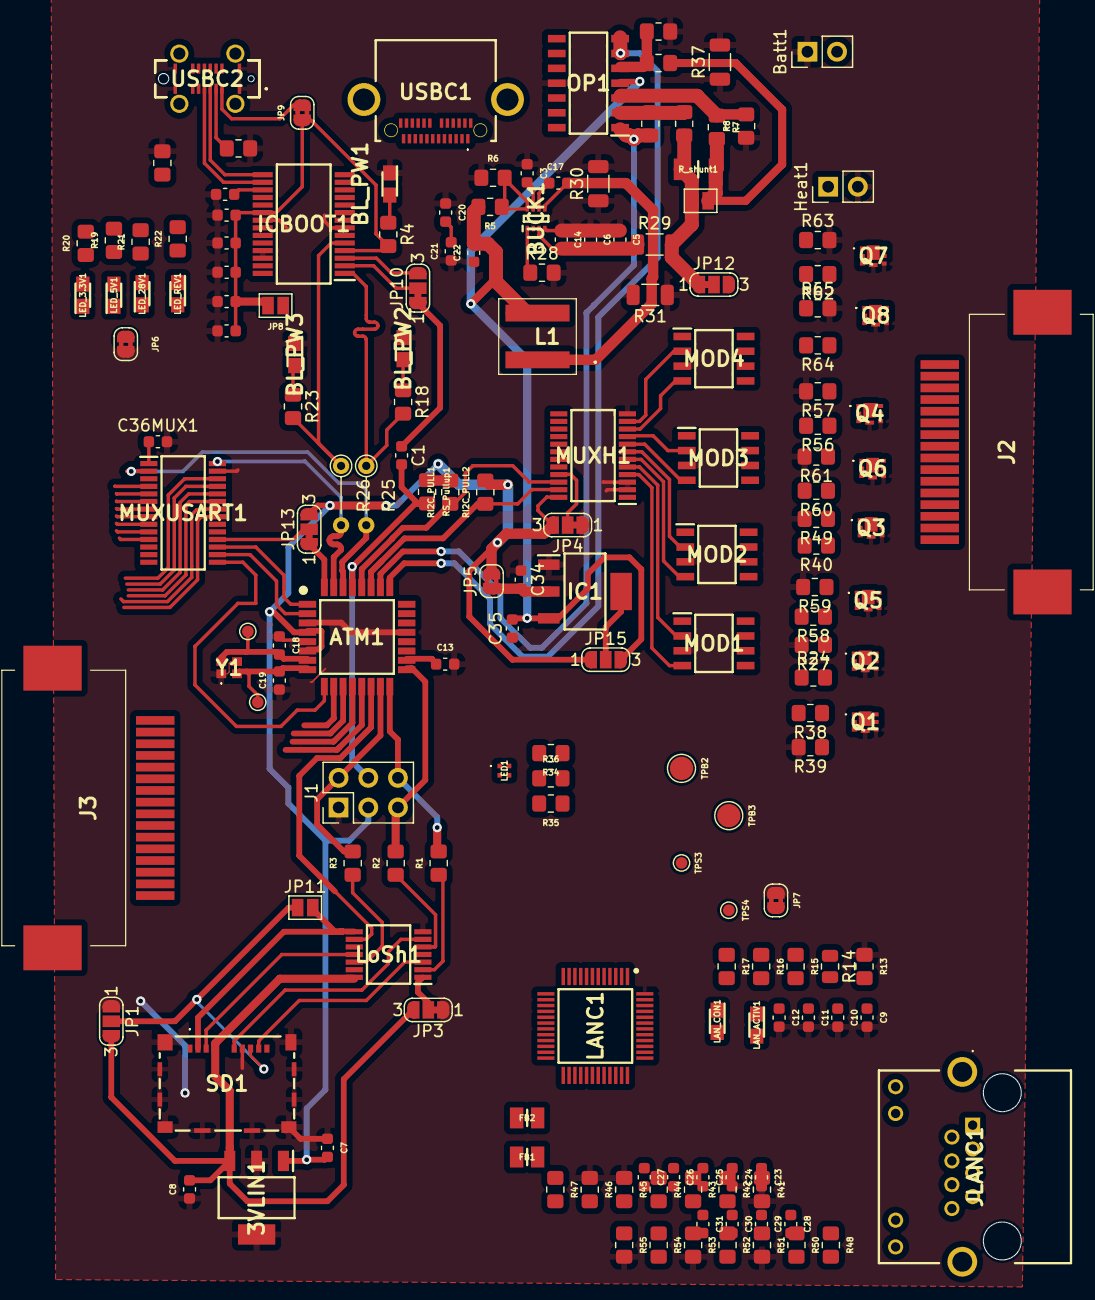
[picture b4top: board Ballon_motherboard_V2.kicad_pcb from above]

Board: 2 copper layers, 170 parts (0 on the bottom side), 124 nets.
